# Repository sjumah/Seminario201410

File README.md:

## Grupo de electrónica - Seminario 201410

Repositorio del grupo de trabajo.

## Contribuidores

- Santiago Jumah Carrion
- Nicolas Zuluaga Botero
- Andres Felipe Ramirez Jaime
- Brian Mauricio Lara Sosa
- Sergio Andres Pedraza Jerez
- Paul Sebastian Guzman Castro
- Santiago Escobar Nassar
- Monica Maria Romero Molano
- Jose Giovanni Vargas Rueda
- David Andres Rodriguez Ramos
- Carol Ximena Naranjo Valero
- Erin Johanna Pinzon Zarate
- Brigitte Stefany Pinto Alejo
- Luis Guillermo Bustamante Torres
- Joseph Reiss Mezrahi
- Rafael Azuero Hurtado
- Gerson David Cruz Capador

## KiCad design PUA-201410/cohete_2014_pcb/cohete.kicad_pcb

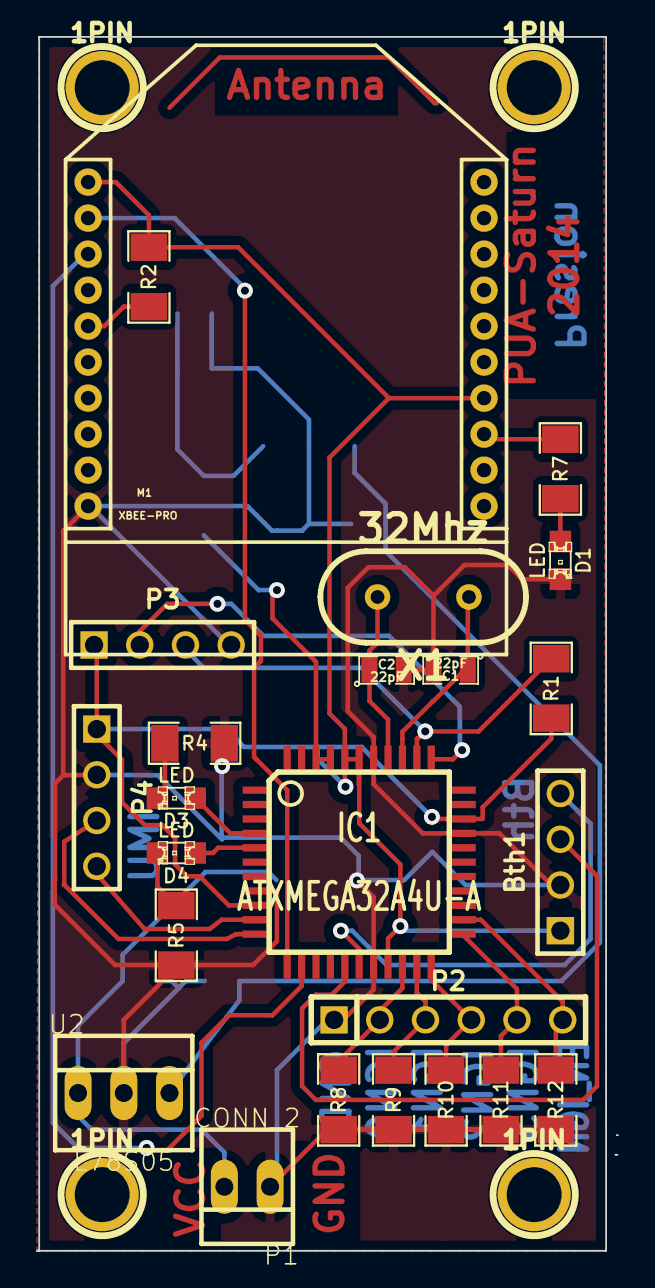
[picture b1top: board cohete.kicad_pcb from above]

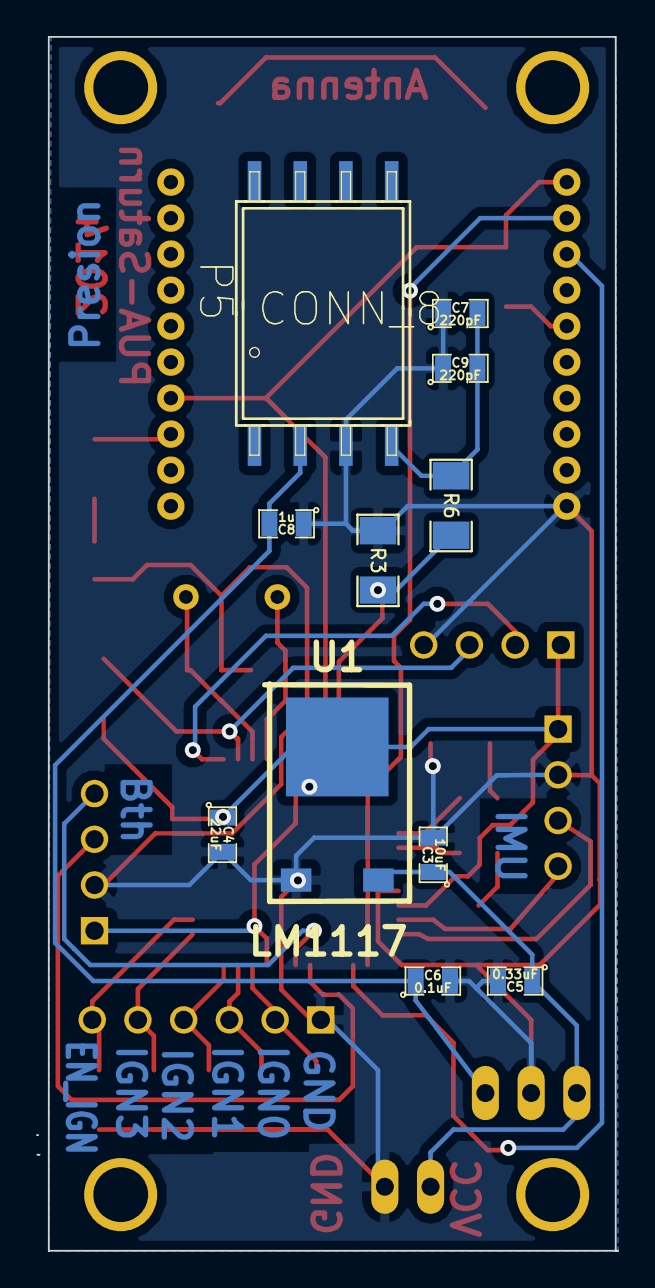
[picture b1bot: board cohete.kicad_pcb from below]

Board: 2 copper layers, 32.3 x 67.4 mm, 39 parts (11 on the bottom side), 28 nets.

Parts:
1PIN, 1PIN#2, 1PIN#3, 1PIN#4: P***; 1pin
Bth1: CONN_4; PIN_ARRAY_4x1
C1, C2: 22pF; SM0805
C3: 10uF; SM0805
C4: 22uF; SM0805
C5: 0.33uF; SM0805
C6: 0.1uF; SM0805
C7, C9: 220pF; SM0805
C8: 1u; SM0805
D1, D3, D4: LED; LED-0805
IC1: ATXMEGA32A4U-A; TQFP44
M1: XBEE-PRO; SparkFun-XBEE-1
P1: CONN_2; PINHEAD1-2
P2: CONN_6; PIN_ARRAY-6X1
P3, P4: CONN_4; PIN_ARRAY_4x1
P5: CONN_8; SparkFun-SO08-GW
R1, R2: 4.7K; SM1206
R3: 2,2k; SM1206
R4, R5, R7: 1K; SM1206
R6: 1,5k; SM1206
R8, R9, R10, R11, R12: 10K; SM1206
U1: LM1117; TO-252
U2: L78S05; PINHEAD1-3
X1: 32Mhz; HC-49V

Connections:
+5V: C6.1, C8.2, P5.2, U2.3
/EN_IGN: IC1.24, P2.6, R12.1
/IGN_0: IC1.20, P2.2, R8.1
/IGN_1: IC1.21, P2.3, R9.1
/IGN_2: IC1.22, P2.4, R10.1
/IGN_3: IC1.23, P2.5, R11.1
/IN_PRESION: IC1.41, IC1.42, R3.1, R6.1
/PDI: IC1.34, P3.2
/RST: IC1.35, P3.3, R1.2
/RX0: IC1.12, M1.2
/RX1: Bth1.3, IC1.16
/SCL: IC1.11, P4.3
/SDA: IC1.10, P4.4
/TX0: IC1.13, M1.3
/TX1: Bth1.4, IC1.17
GND: Bth1.2, C1.2, C2.2, C3.2, C4.2, C5.2, C6.2, C7.1, C8.1, C9.1, D1.2, IC1.8, IC1.18, IC1.30, IC1.38, M1.10, P1.1, P2.1, P3.4, P4.2, P5.3, R3.2, R4.1, R5.1, R8.2, R9.2, R10.2, R11.2, R12.2, U1.1, U2.2
unnamed: M1.5, R2.1
unnamed: M1.13, R7.1
unnamed: D1.1, R7.2
unnamed: D4.2, R5.2
unnamed: D3.1, IC1.4
unnamed: D4.1, IC1.5
unnamed: D3.2, R4.2
unnamed: C1.1, IC1.36, X1.1
unnamed: C2.1, IC1.37, X1.2
unnamed: C3.1, C5.1, P1.2, U1.3, U2.1
unnamed: C7.2, C9.2, P5.4, R6.2
VCC: Bth1.1, C4.1, IC1.9, IC1.19, IC1.31, IC1.39, IC1.40, M1.1, M1.14, P3.1, P4.1, R1.1, R2.2, U1.2

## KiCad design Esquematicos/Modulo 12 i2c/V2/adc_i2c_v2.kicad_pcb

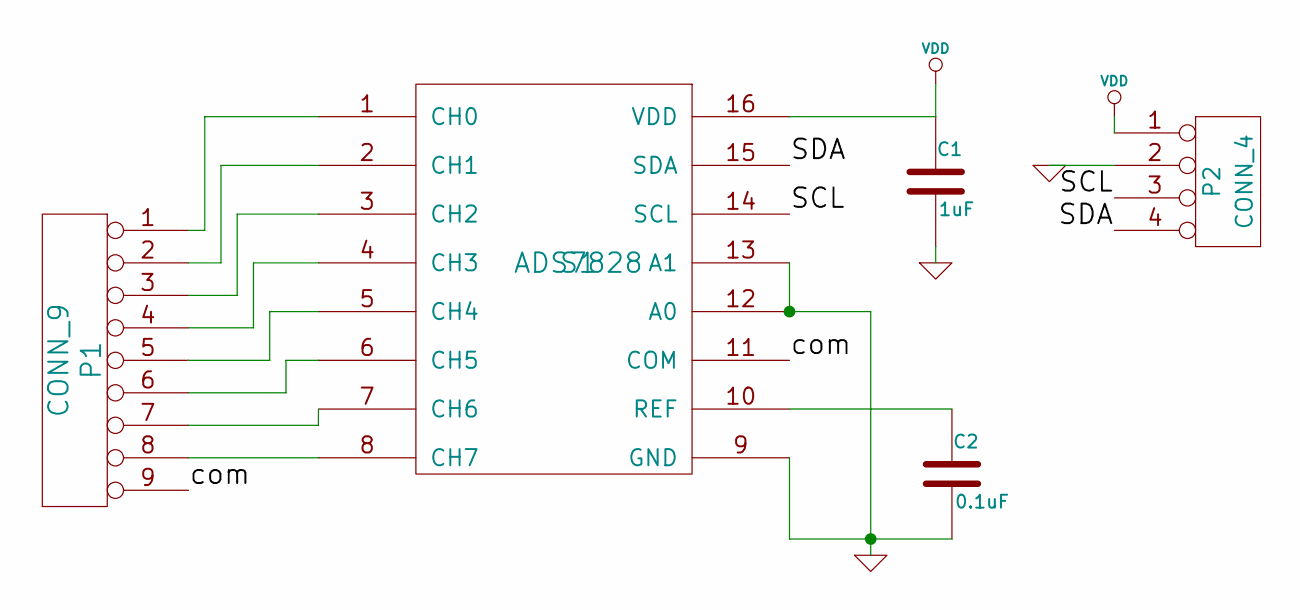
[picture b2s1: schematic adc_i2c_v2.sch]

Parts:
C1: 1uF
C2: 0.1uF
P1: CONN_9
P2: CONN_4
S1: ADS7828

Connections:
/SCL: P2.3, S1.14 (SCL)
/SDA: P2.4, S1.15 (SDA)
/com: P1.9, S1.11 (COM)
GND: C1.2, C2.2, P2.2, S1.9 (GND), S1.12 (A0), S1.13 (A1)
unnamed: P1.7, S1.7 (CH6)
unnamed: P1.8, S1.8 (CH7)
unnamed: P1.6, S1.6 (CH5)
unnamed: P1.1, S1.1 (CH0)
unnamed: P1.2, S1.2 (CH1)
unnamed: P1.3, S1.3 (CH2)
unnamed: P1.4, S1.4 (CH3)
unnamed: P1.5, S1.5 (CH4)
unnamed: C2.1, S1.10 (REF)
VDD: C1.1, P2.1, S1.16 (VDD)

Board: 2 copper layers, 5 parts (0 on the bottom side), 14 nets, no tracks yet.

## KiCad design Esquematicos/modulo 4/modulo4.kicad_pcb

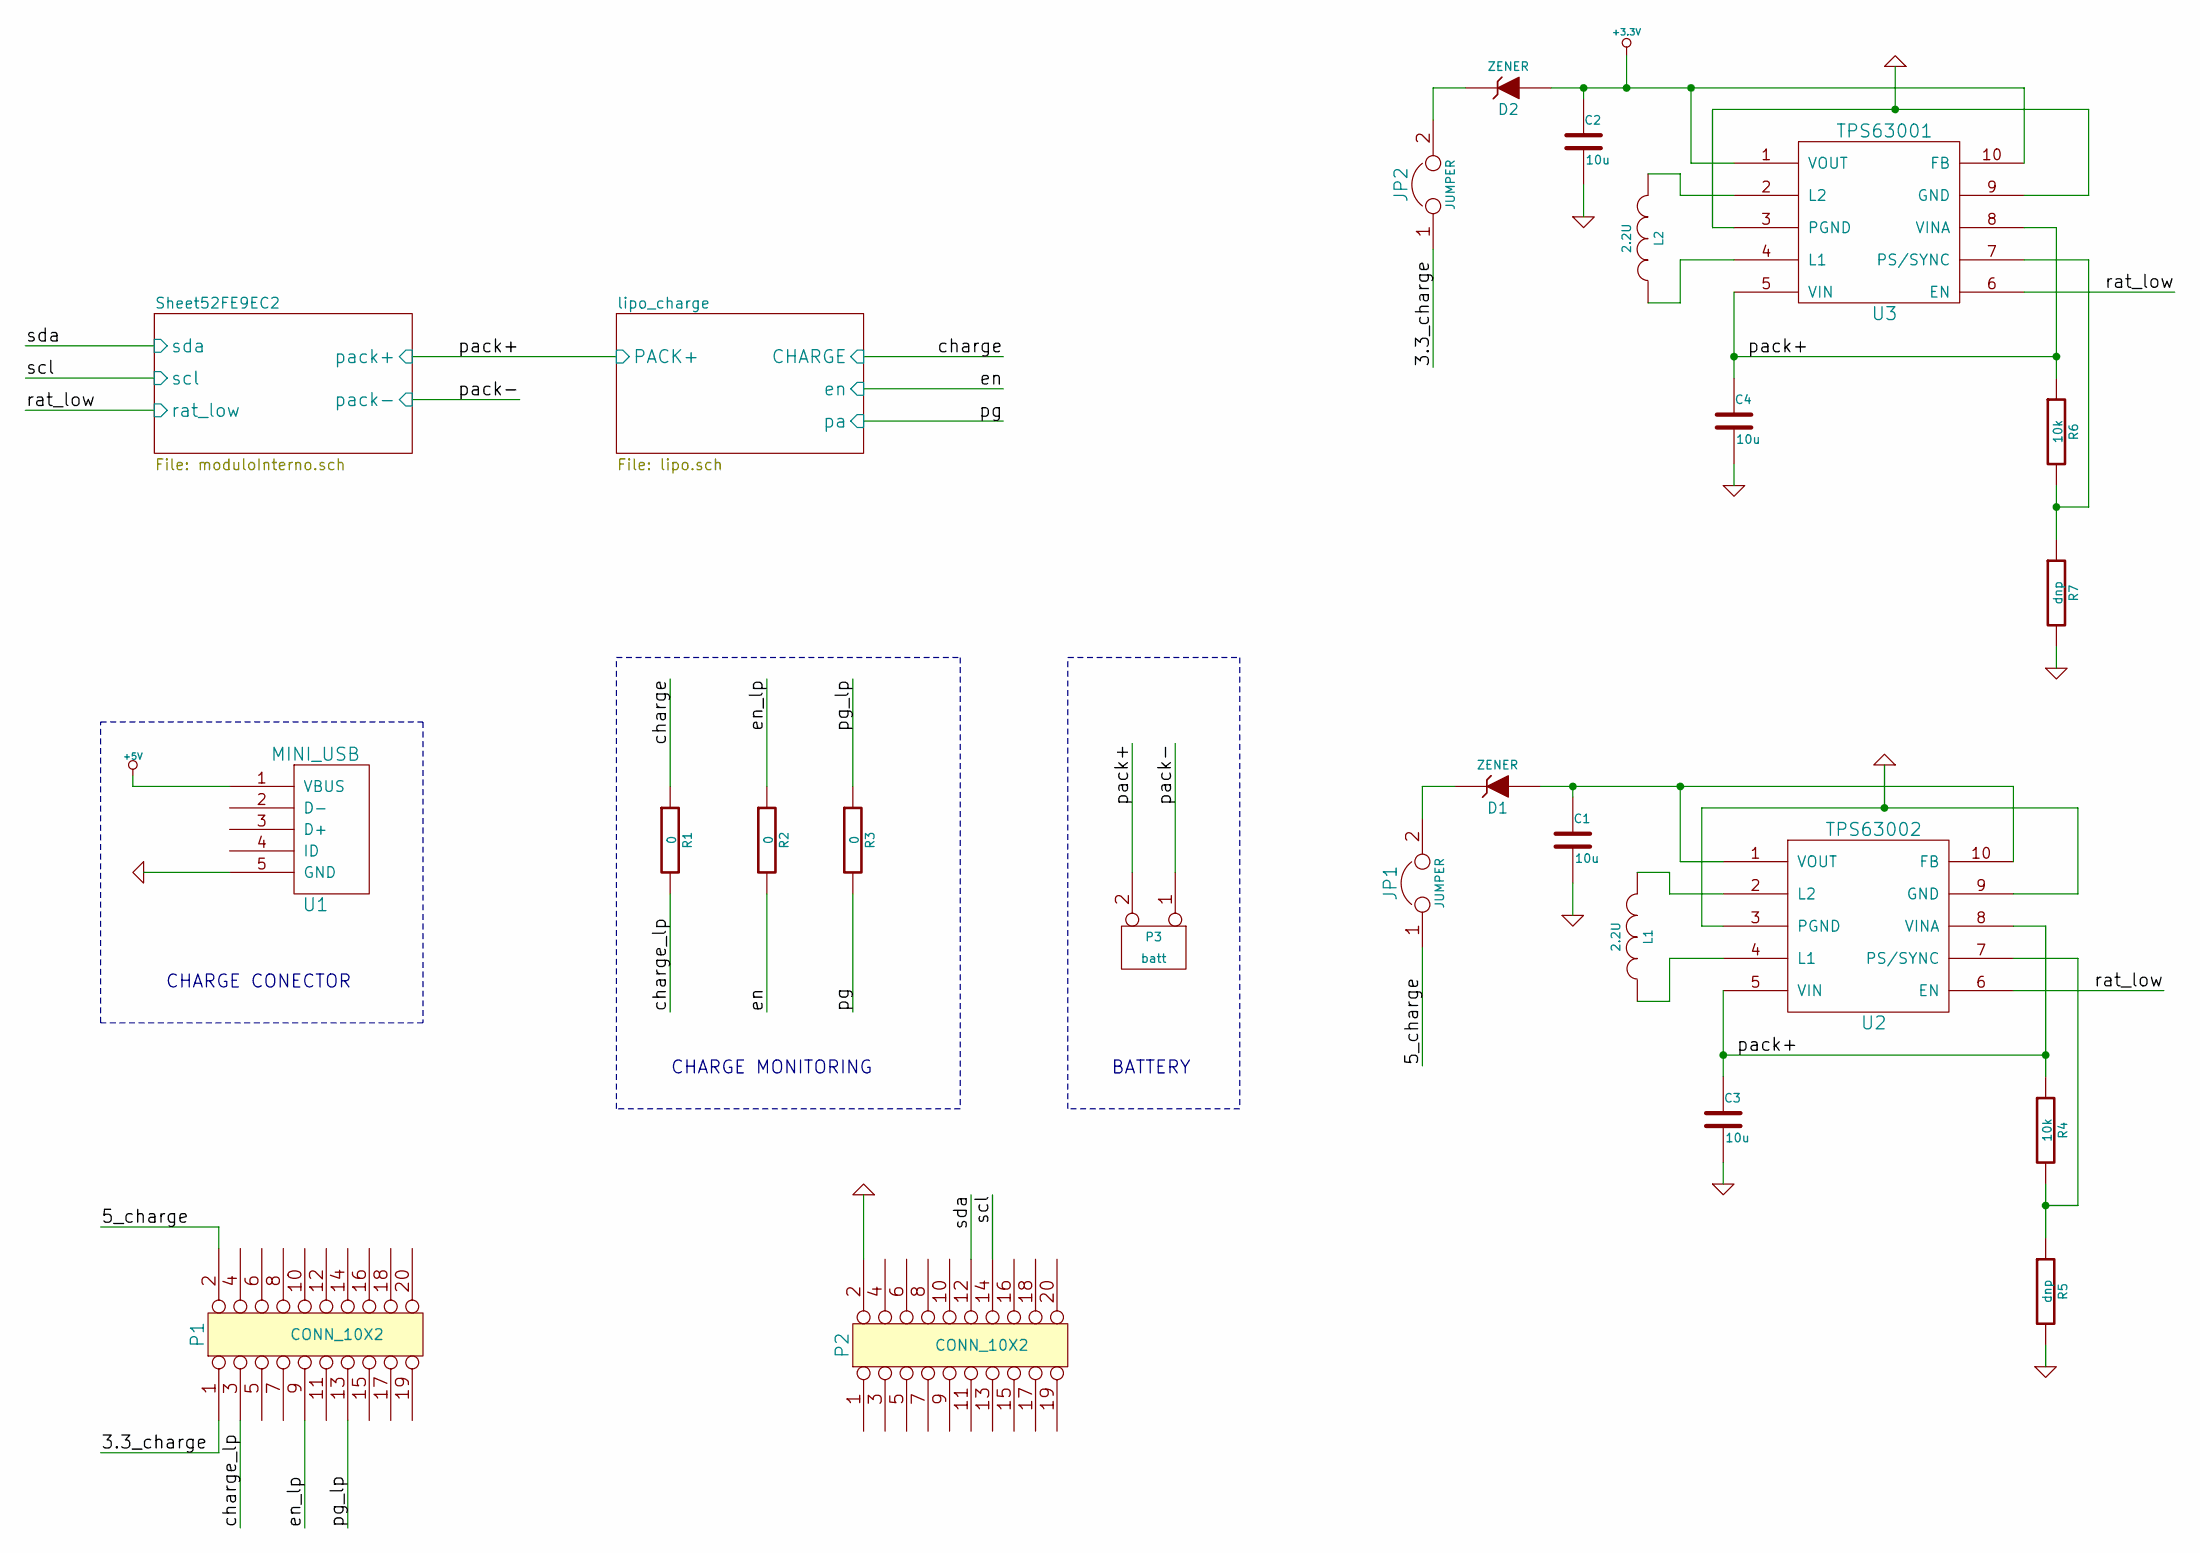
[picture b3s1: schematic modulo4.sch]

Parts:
C1, C2, C3, C4: 10u
D1, D2: ZENER
JP1, JP2: JUMPER
L1, L2: 2.2U
P1, P2: CONN_10X2
P3: batt
R1, R2, R3: 0
R4, R6: 10k
R5, R7: dnp
U1: MINI_USB
U2: TPS63002
U3: TPS63001

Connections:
+3.3V: C2.1, D2.1 (A), U3.1 (VOUT), U3.10 (FB); also elsewhere on the board
+5V: U1.1 (VBUS); also elsewhere on the board
/3.3_charge: JP2.1, P1.1
/5_charge: JP1.1, P1.2
/Sheet52FE9EC2/pack-: P3.1; also elsewhere on the board
/Sheet52FE9EC2/rat_low: U2.6 (EN), U3.6 (EN); also elsewhere on the board
/Sheet52FE9EC2/scl: P2.14; also elsewhere on the board
/Sheet52FE9EC2/sda: P2.12; also elsewhere on the board
/charge_lp: P1.3, R1.2
/en_lp: P1.9, R2.1
/lipo_charge/CHARGE: R1.1; also elsewhere on the board
/lipo_charge/PACK+: C3.1, C4.1, P3.2 (PM), R4.1, R6.1, U2.5 (VIN), U2.8 (VINA), U3.5 (VIN), U3.8 (VINA); also elsewhere on the board
/lipo_charge/en: R2.2; also elsewhere on the board
/lipo_charge/pa: R3.2; also elsewhere on the board
/pg_lp: P1.13, R3.1
GND: C1.2, C2.2, C3.2, C4.2, P2.2, R5.2, R7.2, U1.5 (GND), U2.3 (PGND), U2.9 (GND), U3.3 (PGND), U3.9 (GND); also elsewhere on the board
unnamed: R4.2, R5.1, U2.7 (PS/SYNC)
unnamed: D1.2 (K), JP1.2
unnamed: C1.1, D1.1 (A), U2.1 (VOUT), U2.10 (FB)
unnamed: L1.2, U2.2 (L2)
unnamed: L1.1, U2.4 (L1)
unnamed: L2.1, U3.4 (L1)
unnamed: L2.2, U3.2 (L2)
unnamed: R6.2, R7.1, U3.7 (PS/SYNC)
unnamed: D2.2 (K), JP2.2

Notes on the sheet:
BATTERY
CHARGE MONITORING
CHARGE CONECTOR

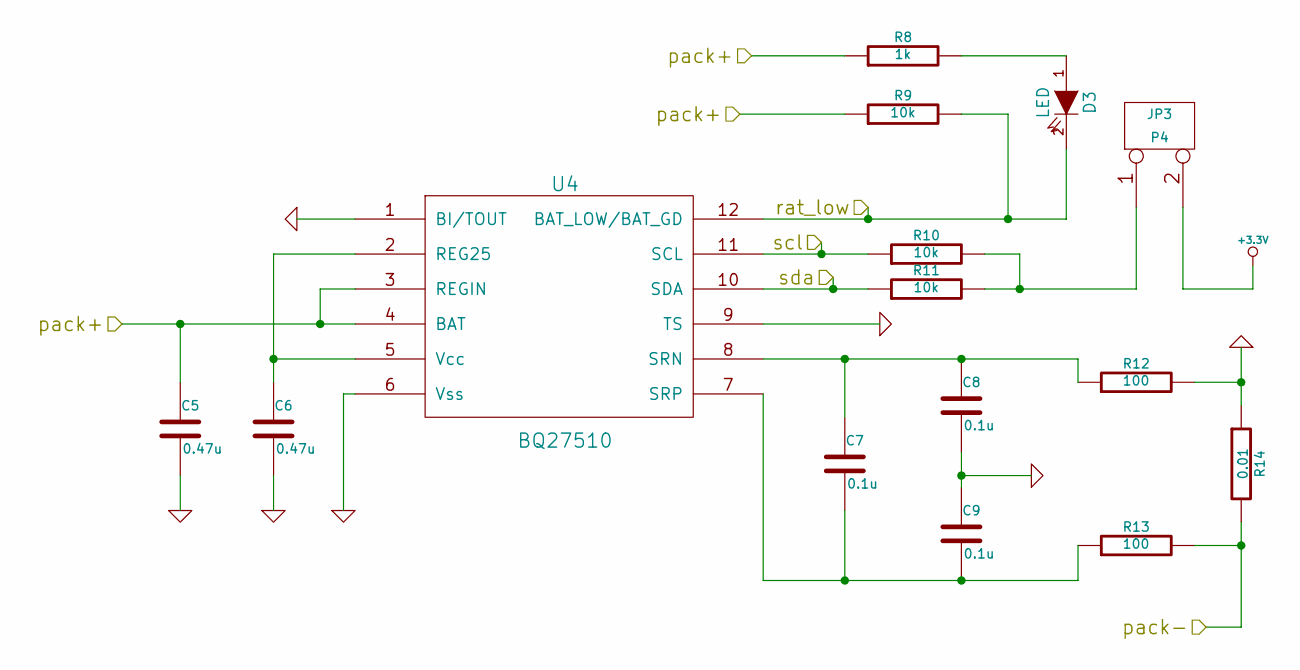
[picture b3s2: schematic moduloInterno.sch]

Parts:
C5, C6: 0.47u
C7, C8, C9: 0.1u
D3: LED
P4: JP3
R8: 1k
R9, R10, R11: 10k
R12, R13: 100
R14: 0.01
U4: BQ27510

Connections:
+3.3V: P4.2 (PM); also elsewhere on the board
/Sheet52FE9EC2/pack-: R13.2, R14.2; also elsewhere on the board
/Sheet52FE9EC2/rat_low: D3.2 (K), R9.2, U4.12 (BAT_LOW/BAT_GD); also elsewhere on the board
/Sheet52FE9EC2/scl: R10.1, U4.11 (SCL); also elsewhere on the board
/Sheet52FE9EC2/sda: R11.1, U4.10 (SDA); also elsewhere on the board
/lipo_charge/PACK+: C5.1, R8.1, R9.1, U4.3 (REGIN), U4.4 (BAT); also elsewhere on the board
GND: C5.2, C6.2, C8.2, C9.1, R12.2, R14.1, U4.1 (BI/TOUT), U4.6 (Vss), U4.9 (TS); also elsewhere on the board
unnamed: C7.2, C9.2, R13.1, U4.7 (SRP)
unnamed: C7.1, C8.1, R12.1, U4.8 (SRN)
unnamed: C6.1, U4.2 (REG25), U4.5 (Vcc)
unnamed: D3.1 (A), R8.2
unnamed: P4.1, R10.2, R11.2

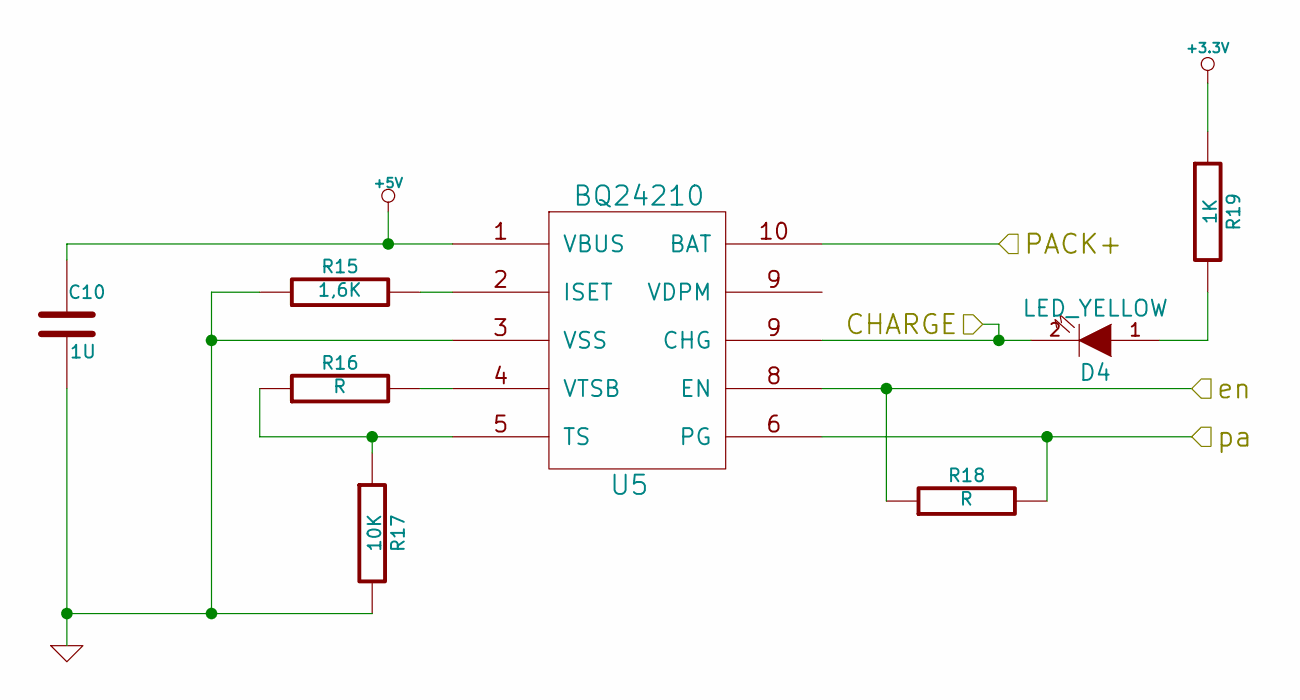
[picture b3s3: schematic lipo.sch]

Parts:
C10: 1U
D4: LED_YELLOW
R15: 1,6K
R16, R18: R
R17: 10K
R19: 1K
U5: BQ24210

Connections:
+3.3V: R19.1; also elsewhere on the board
+5V: C10.1, U5.1 (VBUS); also elsewhere on the board
/lipo_charge/CHARGE: D4.2 (K), U5.9 (CHG); also elsewhere on the board
/lipo_charge/PACK+: U5.10 (BAT); also elsewhere on the board
/lipo_charge/en: R18.1, U5.8 (EN); also elsewhere on the board
/lipo_charge/pa: R18.2, U5.6 (PG); also elsewhere on the board
GND: C10.2, R15.1, R17.2, U5.3 (VSS); also elsewhere on the board
unnamed: R15.2, U5.2 (ISET)
unnamed: D4.1 (A), R19.2
unnamed: R16.1, R17.1, U5.5 (TS)
unnamed: R16.2, U5.4 (VTSB)

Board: 2 copper layers, 46 parts (0 on the bottom side), 34 nets, no tracks yet.

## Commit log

2014-02-03 Archivos de prueba
2014-02-03 prueba
    prueba
2014-02-03 foto de prueba
2014-02-03 borre la foto de prueba
2014-02-03 Mas pruebas
2014-02-03 Archivo de prueba
2014-02-05 prueba
2014-02-05 Diseño Modulo 1
2014-02-06 Revert "Diseño Modulo 1"
    This reverts commit 430f2b2a5d92602d372fbfa4df6ec85dd29e586c.
2014-02-06 Create Modulo1
2014-02-06 Update Modulo1
2014-02-07 pdf de prueba
    flaskjflsakdf
2014-02-07 Borré mis notas :s
    jaja
2014-02-10 Archivo de Prueba
    Hola! Aprendiendo a usar esto! :D
2014-02-12 Caja Negra del GPS
    Subo la caja negra del dispositivo GPS. Es un Quectel L26.
2014-02-12 Adicion de caja negra
2014-02-12 Nombres
2014-02-12 readme
2014-02-13 mas bloques
2014-02-14 tutorial - integrar PCBS
    Muestra cómo integrar 2 pcbs en kicad.
2014-02-14 Cajasnegras, pcb
    cajas negras módulos 9 (corregido) y 12.
    esquemático módulo 12
2014-02-14 avances_pcb
    avance bloques 9 y 12
2014-02-14 imagenes
2014-02-14 mas imagenes
2014-02-14 cambios
2014-02-14 cambio modulo
2014-02-14 actualizacion
2014-02-17 modulo 2 sch
2014-02-17 borrar archivos de prueba
2014-02-17 tutorial de como usar git
2014-02-18 Esquematico terminado
2014-02-20 modulo 6
2014-02-20 recuperacion
2014-02-21 avance módulo 8
    + organización módulos 9 y 12
2014-02-21 Esquemático del GPS
    Faltan algunos valores de resistencias y condensadores.
2014-02-21 screenshot bloque 7 sch
2014-02-21 esquematico bloque 11
2014-03-17 cambio
2014-03-17 prueba modulo 4
2014-05-22 actualizacion mod 8 y 12
    esch mod8 mejorado, versión 2 del mod 12
2014-06-01 pua
    pua 2014 - pcb cohete
2014-06-01 PUA-la carpeta es cohete_2014
    PUA-la carpeta es cohete_2014
2014-06-04 corrección PUA
    con resistencias de pulldown y archivos de fabricación
2014-06-09 código cohete
    código atxmega completo sin probas
2014-06-09 PCB cohete 2014
    última versión PCB cohete
2014-07-01 correcciones varias
2014-07-29 última versión pua
    pua completo: pcb, código avr, código android
2014-07-31 v2.2
2014-08-01 versión final android PUA
2014-08-01 última versión cohete nematodos
2014-08-01 saturn final
2014-08-06 version pua lanzada el 9 de agosto
